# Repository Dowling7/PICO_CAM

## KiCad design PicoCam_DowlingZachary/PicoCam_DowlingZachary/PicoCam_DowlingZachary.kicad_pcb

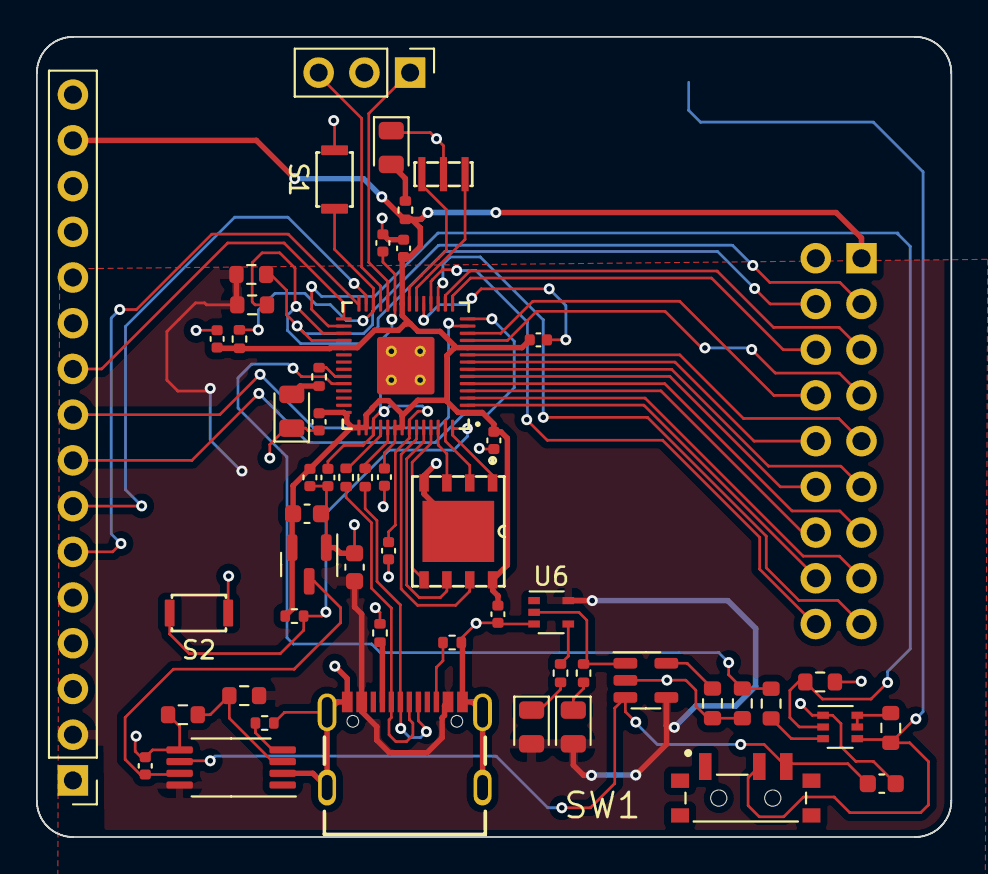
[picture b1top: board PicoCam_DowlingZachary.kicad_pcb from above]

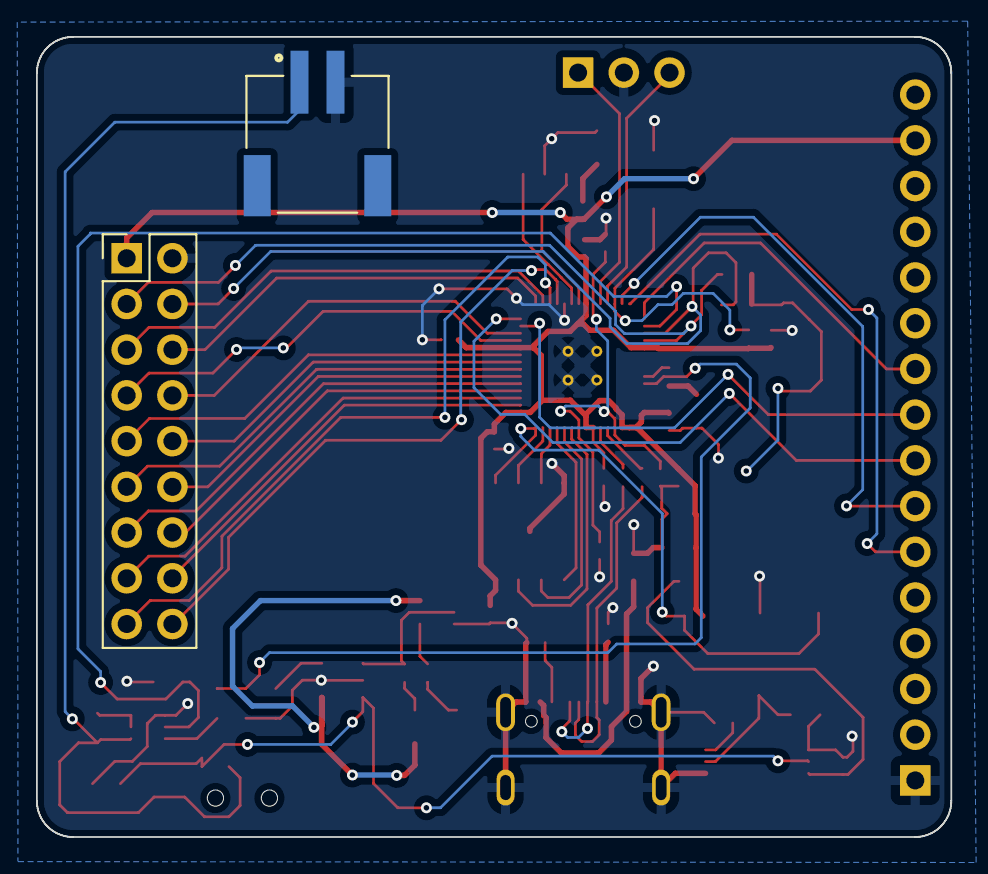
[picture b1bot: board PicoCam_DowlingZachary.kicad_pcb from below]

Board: 2 copper layers, 50.8 x 44.5 mm, 55 parts (2 on the bottom side), 62 nets.

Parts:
C1, C2, C3, C4, C5, C6, C7, C10, C11: 0.1µF; C_0402_1005Metric
C8, C9, C15: 1µF; C_0402_1005Metric
C12, C13, C14: 10µF; C_0603_1608Metric
D1: LED; LED_0805_2012Metric
D2: PWR; LED_0805_2012Metric
D3, D4: D_Small_Filled; LED_0805_2012Metric
J1: USB4105-GF-A
J2: S2B-PH-SM4-TB; JST_S2B-PH-SM4-TB(LF)(SN)
J3: DEBUG; PinHeader_1x03_P2.54mm_Vertical
J_ov7670: Conn_02x09_Odd_Even; PinHeader_2x09_P2.54mm_Vertical
J_st7735r1: Conn_01x16; PinHeader_1x16_P2.54mm_Vertical
Q1: FDG6320C; SOT-363_SC-70-6
R1, R2, R3, R4: 5.1K; R_0402_1005Metric
R5, R6: 27Ω; R_0402_1005Metric
R7, R8: 1K; R_0402_1005Metric
R9, R10, R18: 1k; R_0402_1005Metric
R11, R14, R15, R16: 10k; R_0603_1608Metric
R12: 40k; R_0603_1608Metric
R13: 11k; R_0603_1608Metric
R17: 20k; R_0603_1608Metric
R19, R20: 4.7k; R_0603_1608Metric
S1: RST; KXT321LHS
S2: BOOT; KXT321LHS
SW1: PCM12; SW_PCM12SMTR
U1: W25Q128JV; MIC_WSON-8
U2: RP2040
U3: MCP1702T-3302E_CB; SOT-23
U4: MCP73831T-2ACI_OT; SOT-23-5
U5: TPS2113APW; TSSOP-8_4.4x3mm_P0.65mm
U6: SN74LVC1GU04; SOT-353_SC-70-5
Y1: 12MHz; CSTNE

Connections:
+3V3: C1.2, C2.1, C3.1, C4.1, C5.1, C6.1, C7.1, C8.1, C13.1, J_ov7670.1, J_st7735r1.15, R2.2, R3.2, R8.1, U1.8 (VDD), U2.1 (IOVDD), U2.10 (IOVDD), U2.22 (IOVDD), U2.33 (IOVDD), U2.42 (IOVDD), U2.43 (ADC_AVDD), U2.44 (VREG_VIN), U2.48 (USB_VDD), U2.49 (IOVDD), U3.2 (VOUT)
/BOOT: R3.1, S2.2, U1.1 (~CS), U2.56 (~QSPI_CS)
/GPIO0: J_ov7670.16, U2.2 (GPIO0)
/GPIO1: J_ov7670.15, U2.3 (GPIO1)
/GPIO2: J_ov7670.14, U2.4 (GPIO2)
/GPIO3: J_ov7670.13, U2.5 (GPIO3)
/GPIO4: J_ov7670.12, U2.6 (GPIO4)
/GPIO5: J_ov7670.11, U2.7 (GPIO5)
/GPIO6: J_ov7670.10, U2.8 (GPIO6)
/GPIO7: J_ov7670.9, U2.9 (GPIO7)
/GPIO8: J_ov7670.7, U2.11 (GPIO8)
/GPIO9: J_ov7670.8, U2.12 (GPIO9)
/GPIO10: J_st7735r1.9, U2.13 (GPIO10)
/GPIO11: J_st7735r1.8, U2.14 (GPIO11)
/GPIO12: J_ov7670.6, U2.15 (GPIO12)
/GPIO13: J_ov7670.5, U2.16 (GPIO13)
/GPIO14: J_ov7670.17, U2.17 (GPIO14)
/GPIO15: J_ov7670.18, U2.18 (GPIO15)
/GPIO16: J_st7735r1.7, U2.27 (GPIO16)
/GPIO17: J_st7735r1.6, U2.28 (GPIO17)
/GPIO18: J_st7735r1.10, U2.29 (GPIO18)
/GPIO19: Q1.2, R14.1, U2.30 (GPIO19)
/GPIO20: J_ov7670.4, R20.2, U2.31 (GPIO20)
/GPIO21: J_ov7670.3, J_st7735r1.11, R19.2, U2.32 (GPIO21)
/GPIO22: J_st7735r1.12, U2.34 (GPIO22)
/GPIO23: J_st7735r1.13, U2.35 (GPIO23)
/GPIO24: J_st7735r1.14, U2.36 (GPIO24)
/GPIO25: R7.1, U2.37 (GPIO25)
/GPIO26: R12.2, R13.1, U2.38 (GPIO26/ADC0)
/RUN: R2.1, S1.2, U2.26 (RUN)
/SWCLK: J3.1, U2.24 (SWCLK)
/SWDIO: J3.3, U2.25 (SWDIO)
GND: C1.1, C2.2, C3.2, C4.2, C5.2, C6.2, C7.2, C8.2, C9.2, C10.2, C11.2, C12.1, C13.2, C14.2, C15.2, D1.1 (K), D2.1 (K), J1.A1B12 (GND), J1.B1A12 (GND), J1.S1 (SHELL), J1.S2 (SHELL), J1.S3 (SHELL), J1.S4 (SHELL), J2.2 (-), J3.2, J_ov7670.2, J_st7735r1.1, Q1.1, R1.2, R4.2, R11.2, R12.1, R14.2, R16.1, R18.2, S1.1, S2.1, U1.4 (GND), U1.9 (EP), U2.19 (TESTEN), U2.57 (GND), U3.1 (GND), U4.2 (VSS), U5.2 (~EN), U5.5 (GND), U6.3 (GND), Y1.2
unnamed: C9.1, C10.1, C11.1, U2.23 (DVDD), U2.45 (VREG_VOUT), U2.50 (DVDD)
unnamed: C14.1, SW1.3, U4.3 (VBAT), U5.6 (IN2)
unnamed: C15.1, U3.3 (VIN), U5.7 (OUT)
unnamed: D1.2 (A), R7.2
unnamed: D2.2 (A), R8.2
unnamed: D3.1 (K), R9.1
unnamed: D4.1 (K), R10.1
unnamed: J1.A5 (CC1), R4.1
unnamed: J1.A6 (D+), J1.B6 (D+), R6.1
unnamed: J1.A7 (D-), J1.B7 (D-), R5.1
unnamed: J1.B5 (CC2), R1.1
unnamed: J2.1 (+), Q1.4, R15.1, SW1.2
unnamed: Q1.3, R13.2
unnamed: Q1.5, Q1.6, R15.2
unnamed: R5.2, U2.46 (USB_D-)
unnamed: R6.2, U2.47 (USB_D+)
unnamed: R9.2, U6.4
unnamed: R10.2, U4.1 (STAT), U6.2
unnamed: R11.1, U4.5 (PROG)
unnamed: R16.2, R17.1, U5.3 (VSNS)
unnamed: R18.1, U5.4 (ILIM)
unnamed: U1.2 (DO/IO1), U2.55 (QSPI_SD1)
unnamed: U1.3 (~WP/IO2), U2.54 (QSPI_SD2)
unnamed: U1.5 (DI/IO0), U2.53 (QSPI_SD0)
unnamed: U1.6 (SCK), U2.52 (QSPI_SCLK)
unnamed: U1.7 (~HOLD/IO3), U2.51 (QSPI_SD3)
unnamed: U2.20 (XIN), Y1.1
unnamed: U2.21 (XOUT), Y1.3
VBUS: C12.2, D3.2 (A), D4.2 (A), J1.A4B9 (VBUS), J1.B4A9 (VBUS), J_st7735r1.2, R17.2, R19.1, R20.1, U4.4 (VDD), U5.8 (IN1), U6.5 (Vcc)

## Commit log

2022-11-16 upload
2022-11-18 scheme
2022-11-18 finished mp3_complete
2022-11-25 button
2022-12-16 code line 14 labels
